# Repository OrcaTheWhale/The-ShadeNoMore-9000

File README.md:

# The ShadeNoMore 9000

The ShdeNoMore 9000 is a product designed to make being lazy look cool. Featuring IR receivers like the ones in TV's, you can close and open your curtains using a remote! It's designed to be a household item, featuring common AA batteries. It's also designed in a way where you can put two halves of a design onto each slider piece, and when the product fully closes, it'll connect together and make the piece whole!

Why I made this project:
I wanted to create a household item using a low power microcontroller, and accessible in the way of replacing batteries. Normal people wouldn't have like 3.7V or 7.4V or the sorts of batteries around them, so the project is designed around AA batteries, which are common.

I also made this project because of one thing: The design connection concept. On the sliders, there is clips where you can put two halves of 3D prints or anything like that, and when the curtain fully closes, it'll make the piece whole through the two sliders. That is why the PCB and the remote is and has a design of a Yin and Yang(The PCB technically won't actually match up if you flip the board, but whatever it looks cool). 

How to use it:

**IMPORTANT: The rightside PCB has the IR Receiver soldered onto the BACKSIDE of the PCB, not the front.**

**Your curtain rod MUST be a circle and have a diameter of 1.5cm with the files/CAD provided. If it is a different value, you may adjust sizes accordingly. If your curtain rod is longer or shorter than usual, you can just change the firmware value or change the linkage length.**

Base: Attach both on the rail. The hole tolerance is meant to be tight so it doens't move. Put servo motor in its cubby first. Then, attach the PCB, and the buck converter. Then, slide the servo right fully, and attach the horn on the _outside_ of the base. Then, screw in the servo mount into its respective hole. Put the battery in its cubby and attach the base cover. Repeat for the other base, but mirror the direction, so that the servo horn faces the other way than the previous.

Attach a base on left side of the curtain rod. Make sure the curtain is **open.** Also make sure the base you're attaching has the hole on the servo side. Then, put the sliders in between the innermost curtain slot and the secondmost curtain slot. If that's not how your curtain works, you may attach a clip instead. 

For the right side, use the other base, the one with the hole on the PCB side.

**Design:**

Your design mounts should look like a "lollipop".
The head should be < 4mmx4mm  (no tolerances included), and the stick should be < 3mm. Max mount length: 2cm / 20mm.

On your designs, the sides closest to each other on each mount should be > 10mm.

Take a look at this example(Units in mm): 

You could make it bigger if you wanted:

**BOM**:

You may find the BOM here: [BOM.csv](https://github.com/OrcaTheWhale/The-ShadeNoMore-9000/blob/main/BOM.csv)

The prices are high for small parts due to the prices include shipping.

*Jumper Wires: Realistically, you SHOULD HAVE jumper wires of such short length, about 24-30 AWG.

The Machine Screws are in a kit because the kit has all the different lengths, and nuts needed. Buying each part individually would only increase unnecessary costs.

PCB:

Schematic:

Remote Schematic:

CAD: https://cad.onshape.com/documents/52cdd38d5fc3852829c5e378/w/375261aaecfc0994e985cde6/e/3bd0b3ebbb21816225754123?renderMode=0&uiState=69fbb44bd53928fd316b7f96

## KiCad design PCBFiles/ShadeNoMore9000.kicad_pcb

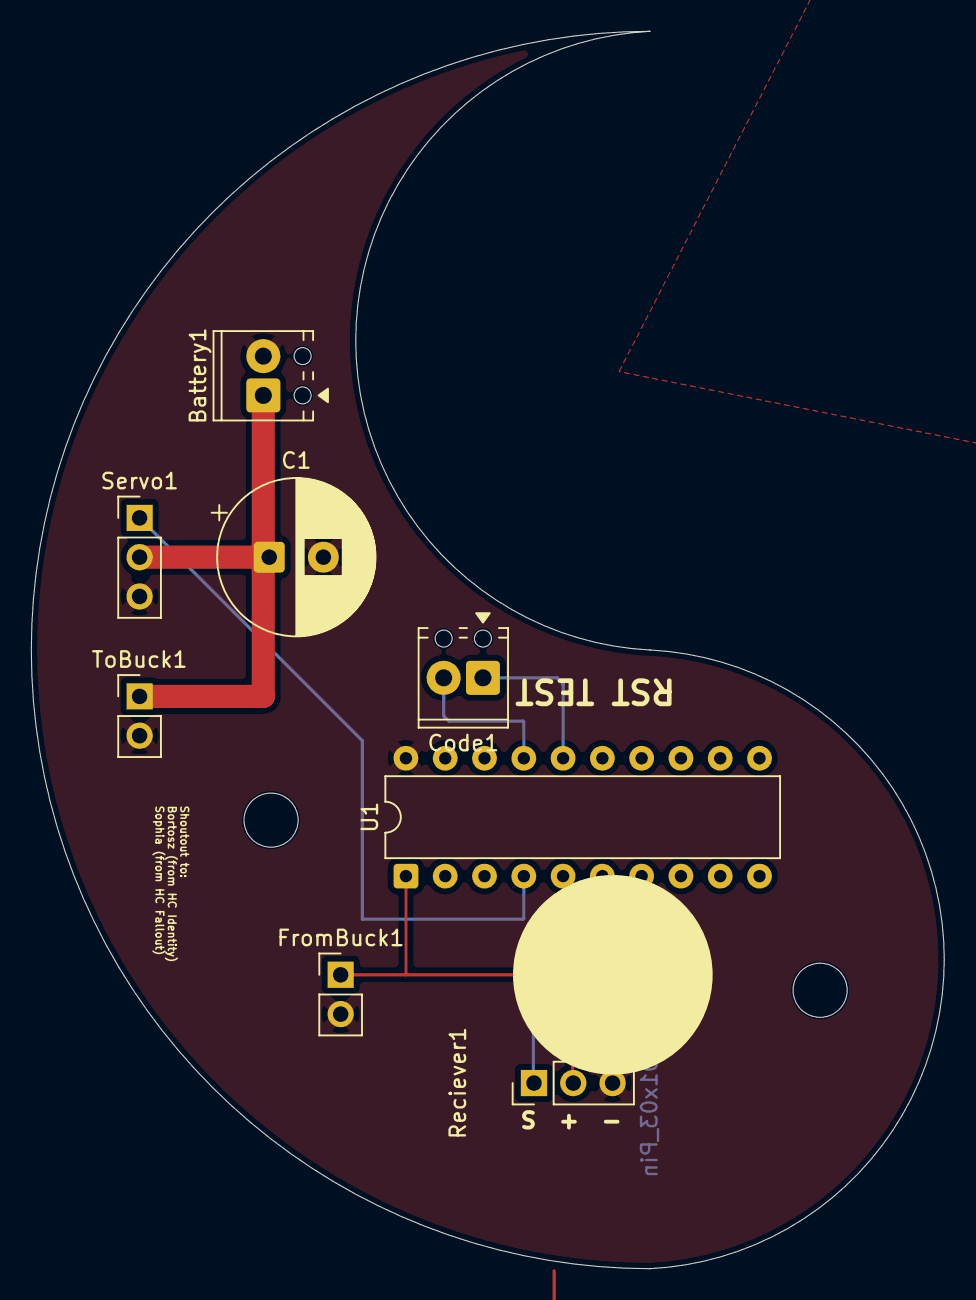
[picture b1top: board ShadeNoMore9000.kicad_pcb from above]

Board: 4 copper layers, 59.0 x 80.0 mm, 8 parts (0 on the bottom side), 7 nets.

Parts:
Battery1: Screw_Terminal_01x02; TerminalBlock_Phoenix_MPT-0,5-2-2.54_1x02_P2.54mm_Horizontal
C1: C_Polarized; CP_Radial_D10.0mm_P3.50mm
Code1: Screw_Terminal_01x02; TerminalBlock_Phoenix_MPT-0,5-2-2.54_1x02_P2.54mm_Horizontal
FromBuck1: Conn_01x02; PinHeader_1x02_P2.54mm_Vertical
Reciever1: Conn_01x03_Pin; PinHeader_1x03_P2.54mm_Vertical
Servo1: Conn_01x03; PinHeader_1x03_P2.54mm_Vertical
ToBuck1: Conn_01x02; PinHeader_1x02_P2.54mm_Vertical
U1: MSP430G2553IN20; DIP-20_W7.62mm

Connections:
+3.3V: FromBuck1.1, Reciever1.2, U1.1 (DVCC)
GND: Battery1.2, C1.2, FromBuck1.2, Reciever1.3, Servo1.3, ToBuck1.2, U1.20 (DVSS)
unnamed: Code1.1, U1.16 (~RST/NMI/SBWTDIO)
unnamed: Code1.2, U1.17 (TEST/SBWTCK)
unnamed: Reciever1.1, U1.6 (TCK/SMCLK/UCB0STE/UCA0CLK/VREF+/VeREF+/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)
unnamed: Servo1.1, U1.4 (UCA0TXD/UCA0SIMO/TA0.1/CA2/A2/P1.2)
VCC: Battery1.1, C1.1, Servo1.2, ToBuck1.1

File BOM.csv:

Component Name,Quanitity,Price,REF,Link
IR Reciever + Transmitter,1,$4.53,,https://www.aliexpress.com/item/32675916539.html?spm=a2g0o.p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
IR Receiver,1,$2.88,Receiver1,https://www.aliexpress.com/item/1930186275.html?spm=2114.120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
MSP430G2553,2,$13.22,U1,https://www.aliexpress.com/item/1005008421058049.html?spm=a2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
MSP430G2553 LaunchPad,1,$27.44,,https://www.aliexpress.com/item/1005007189292097.html?spm=a2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
2 Pin Screw Terminal 2.54mm,2,$3.46,"Code1, Battery1",https://www.aliexpress.com/item/1005002549483233.html?spm=a2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
Male Pin Headers 2.54mm,3,$7.65,"TuBuck1, FromBuck1",https://www.aliexpress.com/item/1005006181780843.html?spm=a2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
Capacitor 16v 470uF,1,$8.28,C1,https://www.aliexpress.com/item/1005006192445408.html?spm=a2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
4x AA Battery Pack,2,$9.99,,https://www.amazon.ca/LAMPVPATH-Battery-Holder-Switch-Leads/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
MG996R (Kit),2,$8.62,,https://www.aliexpress.com/item/1005001878275044.html?spm=a2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
3x AA Battery Pack,1,$3.12,,https://www.aliexpress.com/item/32850286281.html?src=google&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
M3(OD4mm) Heat Set Insert,23,$3.53,,https://www.aliexpress.com/item/1005008666672949.html?spm=a2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
M3 Machine Screw Kit,1,$9.87,,https://www.aliexpress.com/item/1005007021342718.html?spm=a2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
AA Batteries,11,$14.99,,https://www.shoppersdrugmart.ca/duracell-copper-black-aa-8-p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
*Jumper Wires ~3cm,8,$8.41,,https://www.aliexpress.com/item/1005008606823974.html?spm=a2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
CC9000 PCB,2,$3.50,,
PLA Filament,,0.5kg,,
Total,,$146.32,,

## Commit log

2026-05-06 Rename CurtainCloser9000.kicad_pcb to ShadeNoMore9000.kicad_pcb
2026-05-06 Rename CurtainCloser9000.kicad_pro to ShadeNoMore9000.kicad_pro
2026-05-06 Rename CurtainCloser9000.kicad_sch to ShadeNoMore9000.kicad_sch
2026-05-10 Rename CurtainCloserBOM - Sheet1.csv to BOM.csv
